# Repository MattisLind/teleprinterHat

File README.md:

# teleprinterHat
A RaspberryPi HAT that interfaces a old school teleprinter

## History
Some time ago I started planning to get an old Lorenz Lo15 teleprinter working. Then arose the question about how to interface those old machines to the real world. While investigating this I gained quite some knowledge of teleprinter interfacing and Telex networks. For example the normal line voltage of a US teleprinter line is 120VDC and the current is 60 mA.

Preferbly the interfacing should be as simple and small as possible. Using some big expensive 50 Hz 120 VAC transformer, rectifier and 2kOhm 6W resistor was not on the table.

Preferbly the circuit should be able to run off a standard USB charger. I.e. 5V 500mA. Experimenting a bit with a stepup circuit gave that is perfectly possibly to step up 5V to 120V. SO one could ask how could a 5V 500 mA supply be able to supply the power for a 120V 60mA load. Of course it cannot, but the problem lies in the fact tat most of the power is absorbed in the current limiting 2kOhm resistor of the old school circuit. The actual teleprinter has an internal resistance of approximately 100 Ohm. So why 120V? The reason for 120V is to achieve a fast pull of the magnet inside the teleprinter. After the initial pull the steady state voltage drop is between 5 to 10 V at 60mA. 

When I started to work with this project I also made an announcment in the i-Telex forum and got a reply from Jochen that had done something similar and the same point in time. What a coincidence! [piTelex project](https://github.com/fablab-wue/piTelex)

Jochen have compiled a lot of interesting and useful information there but the project is based on a Raspberry Pi and cannt be used stand alone. One of my requirements are that it should be able to run completely stand alone. I don't want the bloat of a Linux kernel just to push a few bytes back and forth!

## Requirments

So I put together a list of requirments

1. Shall only need 5V supply. The generation of up 120V DC is built into the device. Using a step-up converter.
2. Low power consumption. No 6W 2kOhm resistor. Use PWM to control the current through the solenoid. 
3. Configurable for 60mA, 40mA and 20mA current loop.
4. ~~Automatically detect the line voltage to use based on line current and required rise time of current through coil. Measure what kinde of loop inductance there is and adapt to a possibly resistive remote.~~ Deemed not possible with current design.
5. Interface directly to RS-232-E levels on board. (option) using a MAX232 or equivalent and a couple of capacitors
6. Interface directly to USB using FTDI chip on board (option)
7. Do baudot to ASCII conversion locally.
8. Do baudrate adaption locally. Configurable teleprinter baudrate to support at least 45,5, 50, 56, 75, 100 and 110 bps.
9. Configurable uplink RS-232 interface 50, 75, 110, 150, 300 bps to adapt to all sorts of hosts.
10. Dimensions that fits the Rpi Zero preferbly but if it is getting to crammed a standar Rpi HAT is the choice.
11. The RPI should be able to control all settings of the device from GPIO ports. Possibly use SPI to make more advanced configuration possible.
13. LEDs connected to RPi GPIOs to indicate mode or state in RPi Software.
14. Jumpers connected to the RPI GPIOs to control the RPI software and selection om mode of operation.
15. The RPi shall automatically boot up and select operating mode depending on jumpers. For example i-Telex or news RSS, RasPi serial console. No interaction using screen or keyboard connected to the RPi shall be necessary.
16. Relay to support reversal of polarity of the line current (optional)
17. Be able to drive a SSR that can be used to enable power to the teleprinter
18. Diagnostic LED to indicate line malfunction. I.e. to detect an open loop 
19. Current loop interface to support old PDP-11 current loops using opto couplers.
20. Use two 2.5 mm mono plugs for interfacing the teleprinter.
21. Diagnostic LED to indicate what line voltage is selected. Maybe multicolor RGB LED?
22. RX and TX LEDs
23. Support for FSG device (optional)
24. A few test sequences are built in. Continous RY and "The quick brown fox jumps over the lazy dog"
25. Flow control using XON/XOFF, RTS/CTS or DSR/DTR. Selcteable using jumpers. Both via USB/FTDI or RS-232

## Stepup converter

The first thing to verify is that the idea of the step up converter was ok. I did a small circuit board to check the circuit and during this I found that the parameters of the coil si very importantant. It has to have a high enough Isat. Then the choice of MOSFET is important. The MOSFET has to full turn on at only 5V gate voltage which is what is available in this circuit. Thus Vgs(ON) is of high interest. Then to deliver as much of the 5V into the coil means that as little loss of energy in the MOSFET is important. The rDS(ON) is the parameter to look for. 

It turned out that this circuit worked well and could easily deliver 120VDC.

## Using PWM to control the selector magnet.

The main idea with this circuit is to generate the required 60mA with as litle loss as possible. By measuring the current in the loop using a small resistance and then hysteresis regulate the current using a PNP transistor as switch. The current is feed through a small inductor which will not saturate. 

As the switch transistor is swithced on the current in the inductor will increase with time. When it reach the upper hysteresis limit the transistor will switch off. The current in the inductance will continue to flow through the diode and the resistor. As the current reaches the lower limit the transistor will switch on again. 

The receiver magnet inductance will only come into play when going from sending a space bit to a mark bit. Then the large total inductance will keep the regulator switched on for several milliseconds depending on the inductance in the magenet. As soon as the line current level is reached the magnetcoil is fully saturated and will act as a pure resistance. The implementation is based on a op-amp for measuring the differential volatage of the current measuring resistor. Then a fast comparator with a 5% hysterisis band generates a square wave from the incoming sawtooth signal. This squarewave then drives the switch transistors. 

The transistor switch is composed of a PNP transistor as the main switch transistor and a NPN level cvonversion transistor driving the PNP transistor through a resistance.

The reference voltage to the hysteresis comparator is supplied from a PWM signal output of the mikroprocessor. Thereby making it possible to control the current level through software. The PWM signal is low pass filtered in a simple RC network and then buffered through a buffering op-amp.

I did a quick mockup with components at hand but it turned out that the comparator needed to be pretty fast and the transistor switch as well. It simply didn't work very well. I decided to try to do simulations in LTspice before doing further breadboarding. 

Searches on internet gave a decent circuit for a P-MOS FET based switch. Simulations in LTspice gave proper values for resistors and capacitors and it was time to make a peroper board.

Schematic.

The design also included an PNP and NPN transistor to handle keying of the sening signal.

A simple NPN transistor is used to key the current in the loop ON/OFF. This has to be done without any free-wheeling diode since otherwise the release of the magnet when swithcing of the current will be very much delayed and might not even happen at all. 

Initial tests showed good performance. It could regulate the desired current at varying line voltages without any problem.

This picture show the voltage over the measurement resistor. The scale is 100mV per division and the resistor is 51 ohm so the interval it is regulating over is +/- 2mA as designed.

Running the circuit with the actual Lorenz Lo15 teleprinter also yielded good results.

Keying the signal, 90V line voltage, 40 mA line current. The large spikes are created by the selector magnet as the switch cuts off. Had initial problems that the choosen PNP transistor was unable to cope with these. Intalled a 300 V PNP transistor and a MOV to handle the spikes. Worked well. But I am considering using a TVS instead.

This picture shows when regulating the 40mA output to the selector magnet when the line is in marking state.

## Prototyping the Step up converter and current source 

I already did a prototype of the step-up converter. But the MOSFET used was quite big and overdimensioned. I also wanted to use a proper gate driver as well as off load the micro controller doing the chore of keeping the PWM rate continuosly measuring the output voltage. A separate, very small, switch control IC, cheap as well, was a better choice. So I designed another prototype board to test out these concept as well as testing the current loop circuit.

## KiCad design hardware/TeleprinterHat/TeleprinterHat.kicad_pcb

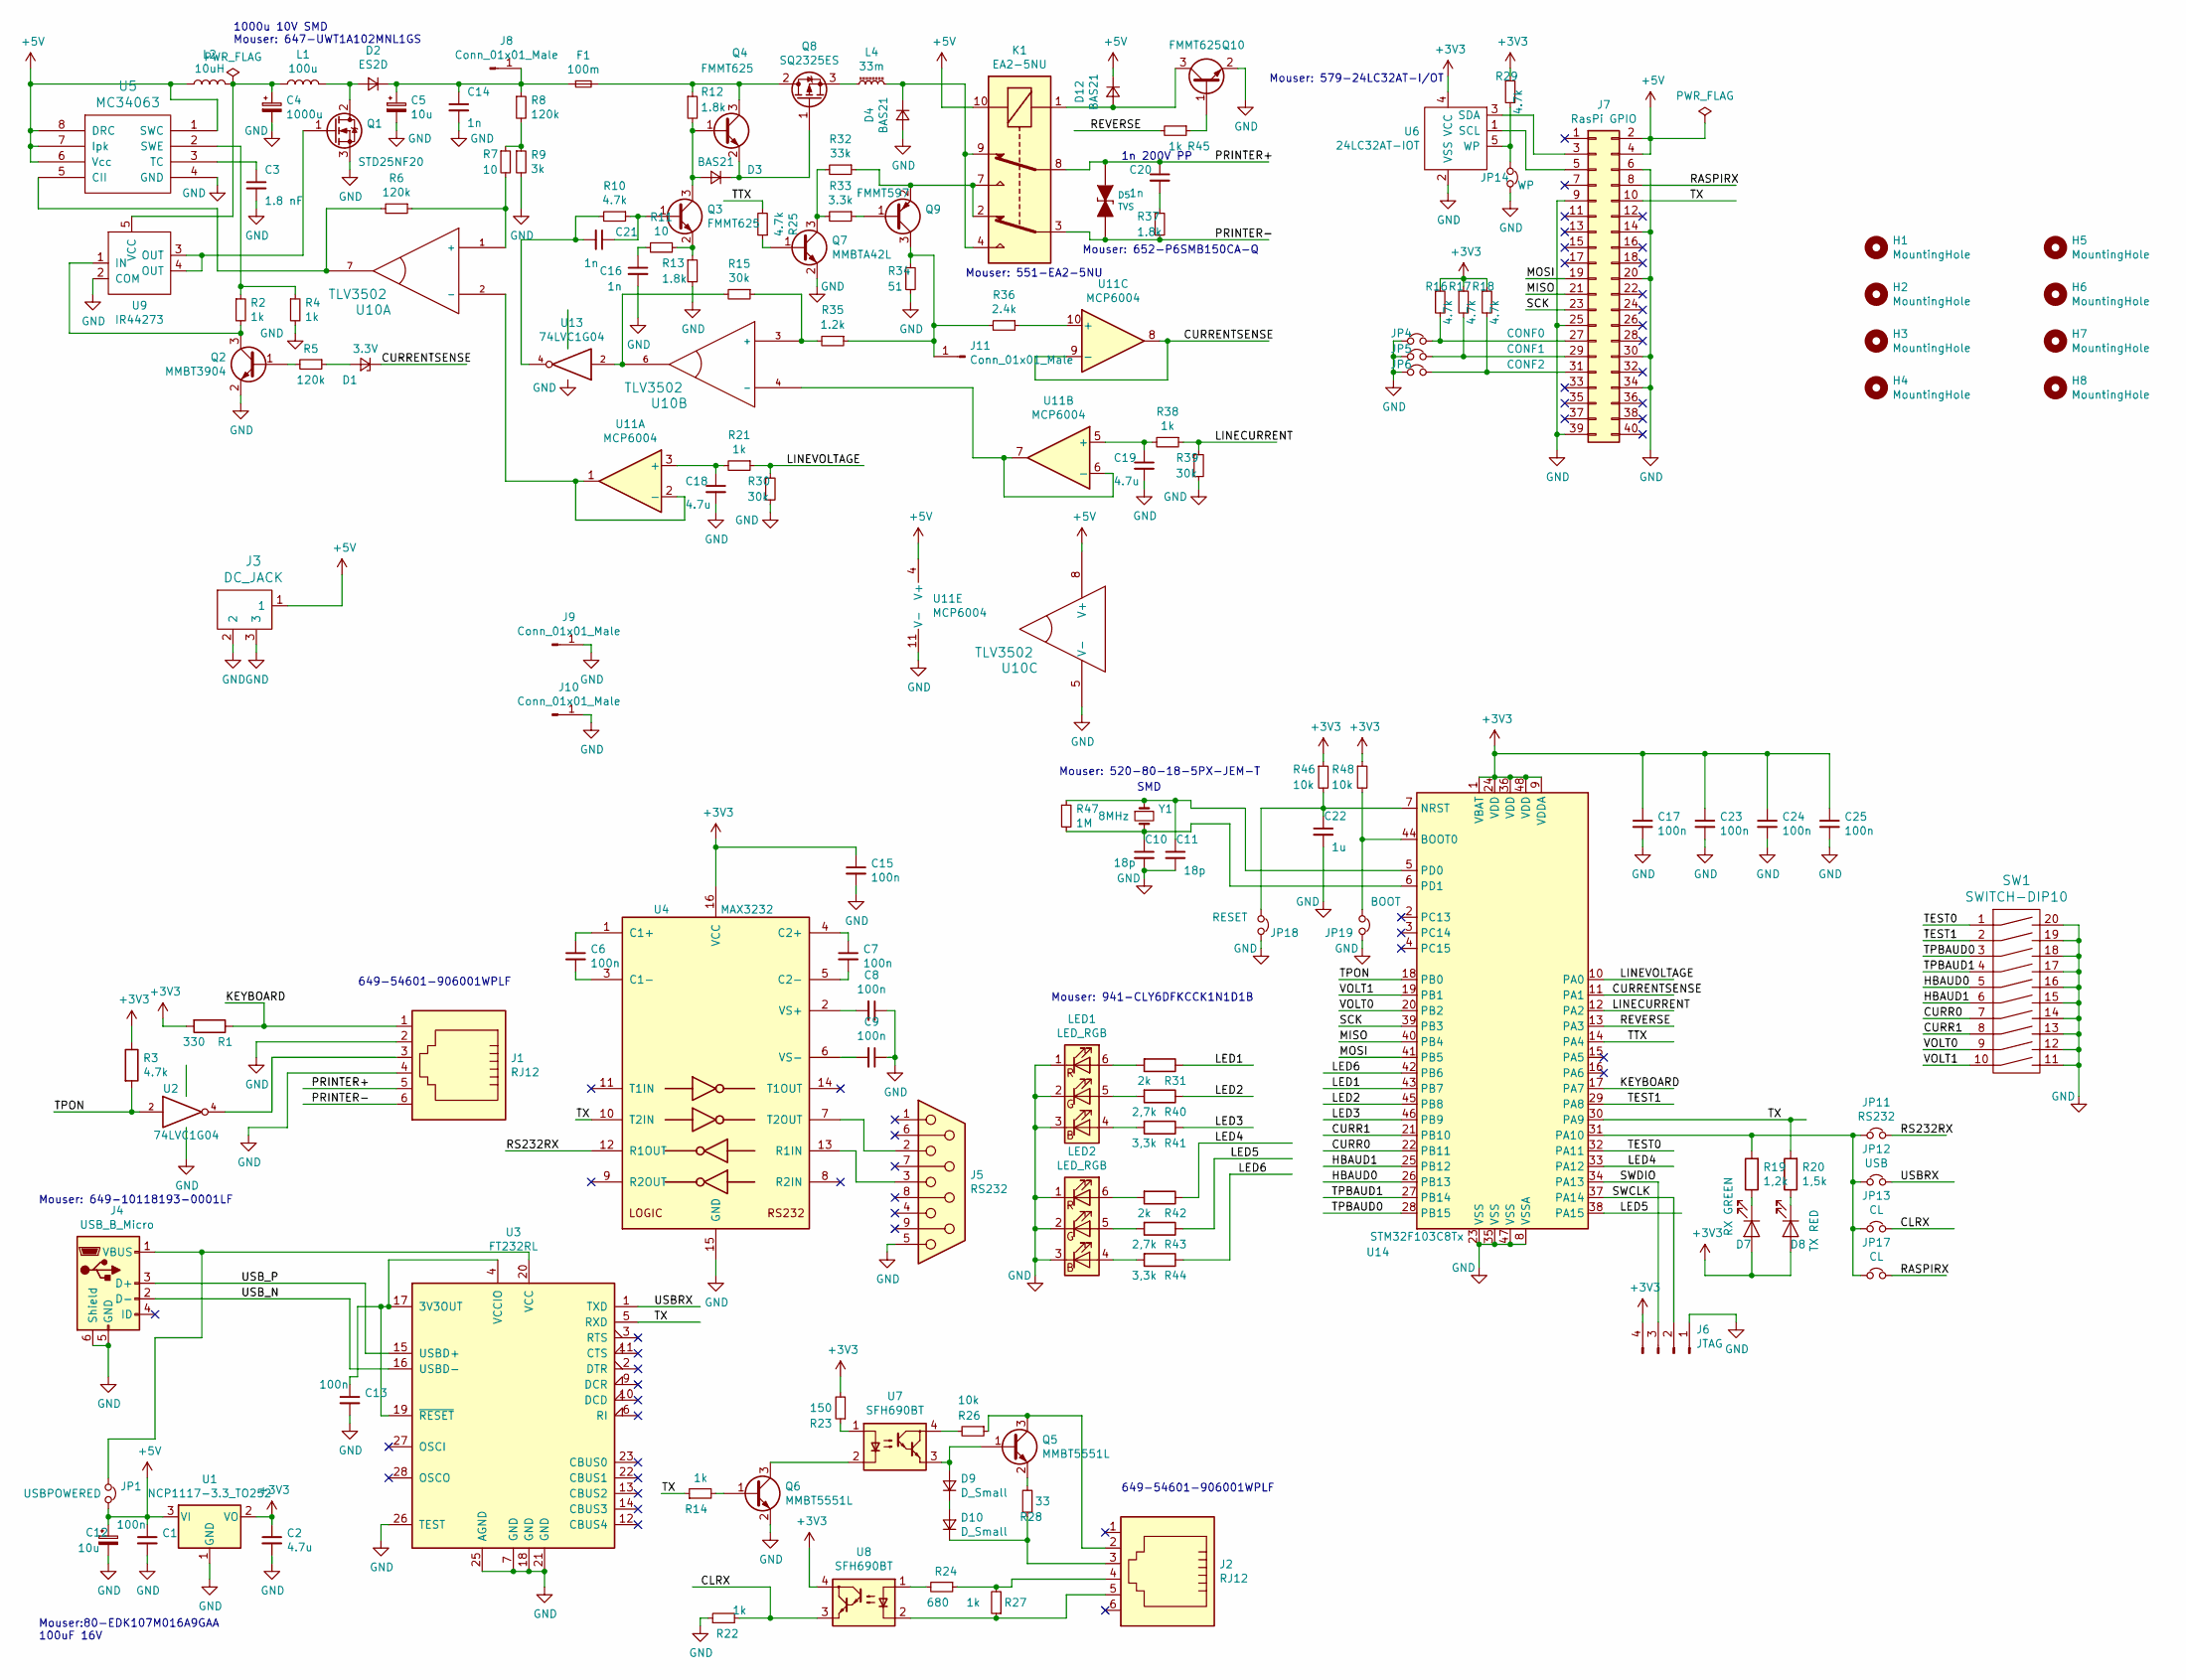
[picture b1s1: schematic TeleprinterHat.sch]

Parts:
C1, C6, C7, C8, C9, C13, C15, C17, C23, C24, C25: 100n; C_0805_2012Metric
C2, C18, C19: 4.7u; C_0805_2012Metric
C3: 1.8 nF; C_0805_2012Metric
C4: 1000u; CP_Elec_10x7.7
C5: 10u; CP_Radial_D8.0mm_P3.50mm
C10, C11: 18p; C_0805_2012Metric
C12: 10u; C_0805_2012Metric
C14, C16, C21: 1n; C_0805_2012Metric
C20: 1n; C_Rect_L7.0mm_W2.0mm_P5.00mm
C22: 1u; C_0805_2012Metric
D1: 3.3V; D_SOD-123
D2: ES2D; D_SMB_Handsoldering
D3, D4, D12: BAS21; SOT-23
D5: TVS; D_SMB_Handsoldering
D7: RX GREEN; LED_0805_2012Metric_Castellated
D8: TX RED; LED_0805_2012Metric_Castellated
D9, D10: D_Small; D_SOD-123
F1: 100m; Fuse_0603_1608Metric_Pad1.05x0.95mm_HandSolder
H1, H2, H3, H4, H5, H6, H7, H8: MountingHole; MountingHole_2.7mm_M2.5
J1, J2: RJ12; RJ12_Amphenol_54601
J3: DC_JACK; BarrelJack_Wuerth_6941xx301002
J4: USB_B_Micro; USB_Micro-B_Amphenol_10103594-0001LF_Horizontal
J5: RS232; DSUB-9_Female_Horizontal_P2.77x2.84mm_EdgePinOffset9.90mm_H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
J6: JTAG; PinHeader_1x04_P2.54mm_Vertical
J7: RasPi GPIO; PinSocket_2x20_P2.54mm_Vertical
J8, J9, J10, J11: Conn_01x01_Male; PinHeader_1x01_P2.54mm_Vertical
JP1: USBPOWERED; PinHeader_1x02_P2.54mm_Vertical
JP4: CONF0; PinHeader_1x02_P2.54mm_Vertical
JP5: CONF1; PinHeader_1x02_P2.54mm_Vertical
JP6: CONF2; PinHeader_1x02_P2.54mm_Vertical
JP11: RS232; PinHeader_1x02_P2.54mm_Vertical
JP12: USB; PinHeader_1x02_P2.54mm_Vertical
JP13, JP17: CL; PinHeader_1x02_P2.54mm_Vertical
JP14: WP; PinHeader_1x02_P2.54mm_Vertical
JP18: RESET; PinHeader_1x02_P2.54mm_Vertical
JP19: BOOT; PinHeader_1x02_P2.54mm_Vertical
K1: EA2-5NU; DIP-10_W7.62mm
L1: 100u; Wurth TIF Radial 1018
L2: 10uH; L_Radial_D7.0mm_P3.00mm
L4: 33m; L_Radial_D12.0mm_P6.00mm_MuRATA_1900R
LED1, LED2: LED_RGB; LED_Avago_PLCC6_3x2.8mm
Q1: STD25NF20; TO-252-3_TabPin2
Q2: MMBT3904; SOT-23
Q3, Q4, Q10: FMMT625; SOT-23
Q5, Q6: MMBT5551L; SOT-23
Q7: MMBTA42L; SOT-23
Q8: SQ2325ES; SOT-23
Q9: FMMT597; SOT-23
R1: 330; R_0805_2012Metric
R2, R4, R14, R21, R22, R27, R38, R45: 1k; R_0805_2012Metric
R3, R10, R16, R17, R18, R25, R29: 4.7k; R_0805_2012Metric
R5, R6, R8: 120k; R_0805_2012Metric
R7, R11: 10; R_0805_2012Metric
R9: 3k; R_0805_2012Metric
R12, R13, R37: 1.8k; R_0805_2012Metric
R15, R30, R39: 30k; R_0805_2012Metric
R19: 1,2k; R_0805_2012Metric
R20: 1,5k; R_0805_2012Metric
R23: 150; R_0805_2012Metric
R24: 680; R_0805_2012Metric
R26, R46, R48: 10k; R_0805_2012Metric
R28: 33; R_0805_2012Metric
R31, R42: 2k; R_0805_2012Metric
R32: 33k; R_0805_2012Metric
R33: 3.3k; R_0805_2012Metric
R34: 51; R_0805_2012Metric
R35: 1.2k; R_0805_2012Metric
R36: 2.4k; R_0805_2012Metric
R40, R43: 2,7k; R_0805_2012Metric
R41, R44: 3,3k; R_0805_2012Metric
R47: 1M; R_0805_2012Metric
SW1: SWITCH-DIP10; DIP-20_W7.62mm
U1: NCP1117-3.3_TO252; TO-252-2
U2, U13: 74LVC1G04; SOT-23-5_HandSoldering
U3: FT232RL; SSOP-28_5.3x10.2mm_P0.65mm
U4: MAX3232; SOIC-16_3.9x9.9mm_P1.27mm
U5: MC34063; SOIC-8_3.9x4.9mm_P1.27mm
U6: 24LC32AT-IOT; SOT-23-5_HandSoldering
U7, U8: SFH690BT; SO-4_4.4x3.6mm_P2.54mm
U9: IR44273; SOT-23-5_HandSoldering
U10: TLV3502; SOT-23-8_Handsoldering
U11: MCP6004; SOIC-14_3.9x8.7mm_P1.27mm
U14: STM32F103C8Tx; LQFP-48_7x7mm_P0.5mm
Y1: 8MHz; Crystal_SMD_HC49-SD

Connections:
+5V: C1.1, C12.1, D12.1 (K), J3.1, J7.2, J7.4, JP1.2, K1.10, L2.1, U1.3 (VI), U5.1 (SWC), U5.6 (Vcc), U5.7 (Ipk), U5.8 (DRC), U10.8 (V+), U11.4 (V+)
/CLRX: JP13.2, R22.2, U8.3
/CURR0: SW1.7, U14.22 (PB11)
/CURR1: SW1.8, U14.21 (PB10)
/CURRENTSENSE: D1.1 (K), U11.8, U11.9 (-), U14.11 (PA1)
/HBAUD0: SW1.5, U14.26 (PB13)
/HBAUD1: SW1.6, U14.25 (PB12)
/KEYBOARD: J1.1, R1.1, U14.17 (PA7)
/LED1: R31.1, U14.43 (PB7)
/LED2: R40.1, U14.45 (PB8)
/LED3: R41.1, U14.46 (PB9)
/LED4: R42.1, U14.33 (PA12)
/LED5: R43.1, U14.38 (PA15)
/LED6: R44.1, U14.42 (PB6)
/LINECURRENT: R38.1, R39.1, U14.12 (PA2)
/LINEVOLTAGE: R21.1, R30.1, U14.10 (PA0)
/MISO: J7.21, U14.40 (PB4)
/MOSI: J7.19, U14.41 (PB5)
/PRINTER+: C20.1, D5.1 (A), J1.5, K1.8
/PRINTER-: D5.2 (K), J1.6, K1.3, R37.2
/RASPIRX: J7.8, JP17.2
/REVERSE: R45.2, U14.13 (PA3)
/RS232RX: JP11.2, U4.12 (R1OUT)
/SCK: J7.23, U14.39 (PB3)
/TEST0: SW1.1, U14.32 (PA11)
/TEST1: SW1.2, U14.29 (PA8)
/TPBAUD0: SW1.3, U14.28 (PB15)
/TPBAUD1: SW1.4, U14.27 (PB14)
/TPON: R3.2, U2.2, U14.18 (PB0)
/TTX: R25.2, U14.14 (PA4)
/TX: J7.10, R14.1, R20.2, U3.5 (RXD), U4.10 (T2IN), U14.30 (PA9)
/USBRX: JP12.2, U3.1 (TXD)
/USB_N: J4.2 (D-), U3.16 (USBD-)
/USB_P: J4.3 (D+), U3.15 (USBD+)
/VOLT0: SW1.9, U14.20 (PB2)
/VOLT1: SW1.10, U14.19 (PB1)
unnamed: C3.1, U5.3 (TC)
unnamed: C4.1, L1.1, L2.2, U9.5 (VCC)
unnamed: C6.1, U4.1 (C1+)
unnamed: C6.2, U4.3 (C1-)
unnamed: C7.1, U4.4 (C2+)
unnamed: C7.2, U4.5 (C2-)
unnamed: C8.2, U4.2 (VS+)
unnamed: C9.2, U4.6 (VS-)
unnamed: C10.1, R47.2, U14.6 (PD1), Y1.2
unnamed: C11.1, R47.1, U14.5 (PD0), Y1.1
unnamed: C13.1, U3.4 (VCCIO), U3.17 (3V3OUT), U3.19 (~RESET~)
unnamed: C5.1, C14.1, D2.1 (K), F1.1, J8.1, R8.1
unnamed: C16.1, R11.2
unnamed: C18.1, R21.2, U11.3 (+)
unnamed: C19.1, R38.2, U11.5 (+)
unnamed: C20.2, R37.1
unnamed: C21.1, Q3.1 (B), R10.1
unnamed: C21.2, R10.2, U13.4
unnamed: C22.1, JP18.1, R46.2, U14.7 (NRST)
unnamed: D1.2 (A), R5.1
unnamed: D2.2 (A), L1.2, Q1.2 (D)
unnamed: D3.1 (K), Q4.2 (E), Q8.1 (G)
unnamed: D3.2 (A), Q3.3 (C), Q4.1 (B), R12.2
unnamed: D4.1 (K), K1.4, K1.9, L4.2
unnamed: D9.2 (A), Q5.1 (B), U7.3
unnamed: D10.1 (K), J2.3, R28.1
unnamed: D9.1 (K), D10.2 (A)
unnamed: D12.2 (A), K1.1, Q10.3 (C)
unnamed: F1.2, Q4.3 (C), Q8.2 (D), R12.1
unnamed: J1.3, U2.4
unnamed: J2.2, Q5.3 (C), R26.1
unnamed: J2.4, R24.1, R27.2
unnamed: J2.5, R27.1, U8.2
unnamed: J4.1 (VBUS), JP1.1, U3.20 (VCC)
unnamed: J5.2, U4.7 (T2OUT)
unnamed: J5.3, U4.13 (R1IN)
unnamed: J7.3, U6.3 (SDA)
unnamed: J7.5, U6.1 (SCL)
unnamed: J7.27, JP4.2, R16.2
unnamed: J7.29, JP5.2, R17.2
unnamed: J7.31, JP6.2, R18.2
unnamed: J11.1, Q9.3 (C), R34.1, R35.1, R36.2
unnamed: JP11.1, JP12.1, JP13.1, JP17.1, R19.2, U14.31 (PA10)
unnamed: JP14.1, R29.2, U6.5 (WP)
unnamed: JP19.1, R48.2, U14.44 (BOOT0)
unnamed: K1.2, K1.7, Q9.2 (E), R32.1
unnamed: L4.1, Q8.3 (S)
unnamed: LED1.4 (BA), R41.2
unnamed: LED1.5 (GA), R40.2
unnamed: LED1.6 (RA), R31.2
unnamed: LED2.4 (BA), R44.2
unnamed: LED2.5 (GA), R43.2
unnamed: LED2.6 (RA), R42.2
unnamed: Q1.1 (G), U9.3 (OUT), U9.4 (OUT)
unnamed: Q2.1 (B), R5.2
unnamed: Q2.3 (C), R2.2, U9.1 (IN)
unnamed: Q3.2 (E), R11.1, R13.1
unnamed: Q5.2 (E), R28.2
unnamed: Q6.1 (B), R14.2
unnamed: Q6.3 (C), U7.2
unnamed: Q7.1 (B), R25.1
unnamed: Q7.3 (C), R32.2, R33.2
unnamed: Q9.1 (B), R33.1
unnamed: Q10.1 (B), R45.1
unnamed: R2.1, R4.1, U5.2 (SWE)
unnamed: R6.1, R7.2, U10.1 (+)
unnamed: R6.2, U5.5 (CII), U10.7
unnamed: R7.1, R8.2, R9.1
unnamed: R15.1, R35.2, U10.3 (+)
unnamed: R15.2, U10.6, U13.2
unnamed: R23.1, U7.1
unnamed: R24.2, U8.1
unnamed: R26.2, U7.4
unnamed: R36.1, U11.10 (+)
unnamed: U10.2 (-), U11.1, U11.2 (-)
unnamed: U10.4 (-), U11.6 (-), U11.7

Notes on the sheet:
Mouser: 551-EA2-5NU
Mouser: 941-CLY6DFKCCK1N1D1B
SMD
1n 200V PP
Mouser: 649-10118193-0001LF
1000u 10V SMD Mouser: 647-UWT1A102MNL1GS
Mouser: 520-80-18-5PX-JEM-T
Mouser: 579-24LC32AT-I/OT
Mouser:80-EDK107M016A9GAA 100uF 16V
Mouser: 652-P6SMB150CA-Q
649-54601-906001WPLF

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
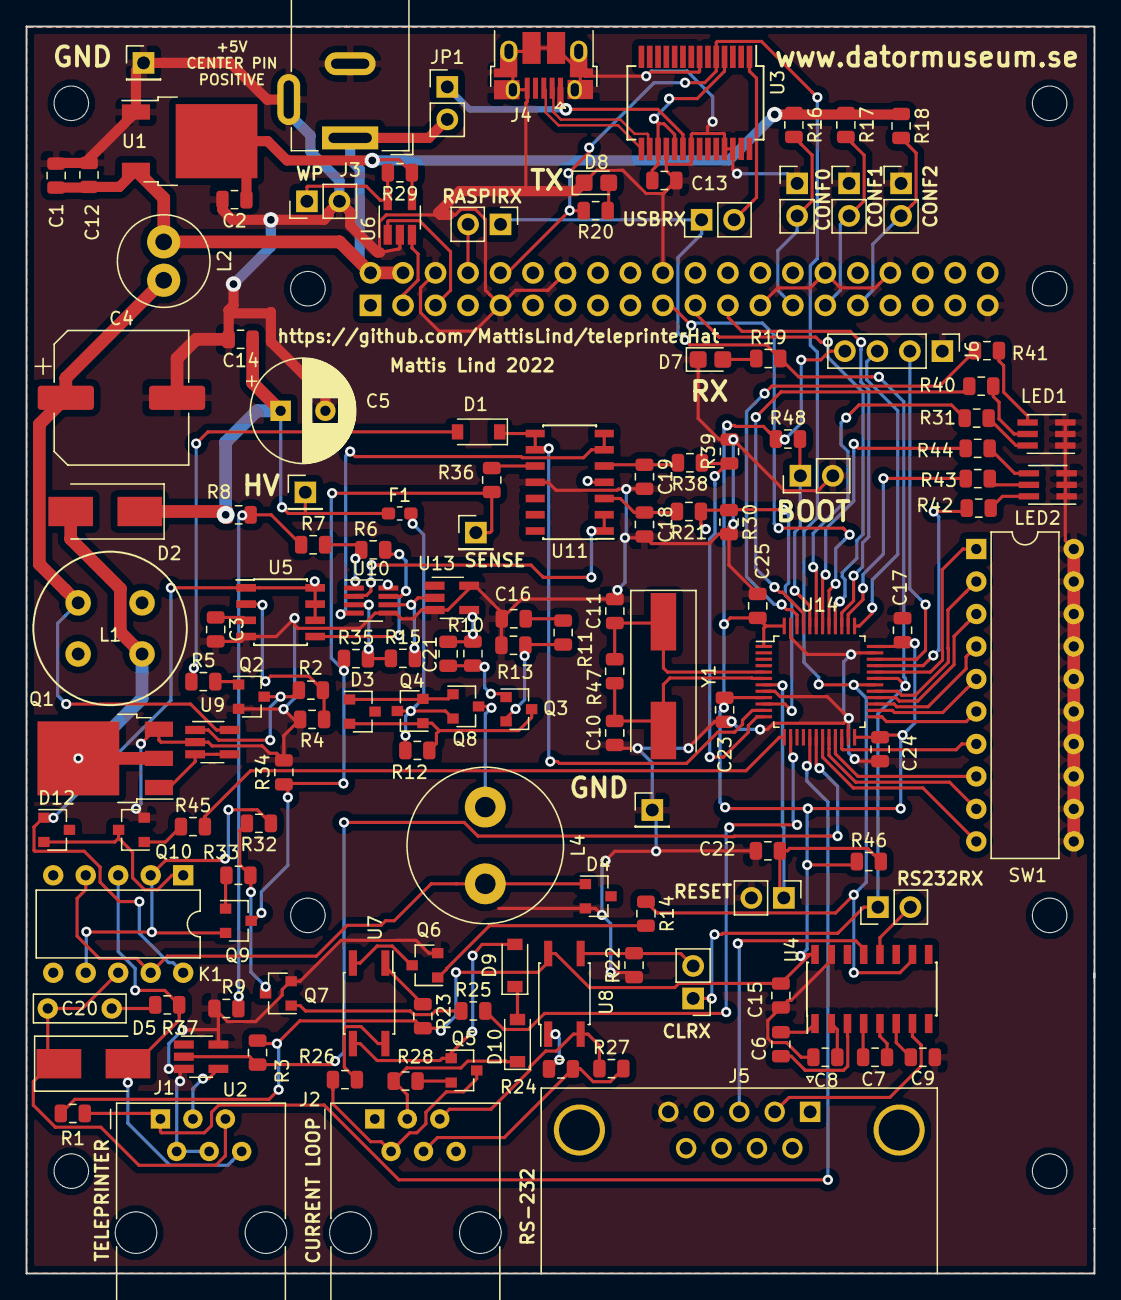
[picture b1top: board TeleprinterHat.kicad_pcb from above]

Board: 2 copper layers, 83.5 x 97.5 mm, 145 parts (1 on the bottom side), 118 nets.

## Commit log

2019-04-01 First commit of requiremnents.
2019-04-01 Adding info on the Step up converter and PVM idea.
2019-06-21 Just a quick hack for testing.
2019-06-21 Added more pictures on the prototypes
2019-06-21 Fixed the wrong picture.
2019-06-21 Added the prototype step up converter schematic
2019-06-21 LO15 not LO15b
2019-06-22 Added a small stupid unit test to see that the code for handling baudot conversionand buffering worked. Buffering did work but not the baudot conversion so some bugfixing was needed, which havt to go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
2019-06-22 Added code and test case for the tx state machine
2019-06-23 First try at a uart rx receiver.
2019-06-23 Moving files a bit.
2019-06-23 Major refactoring into several differnt modules.
2019-06-24 Changed name.
2019-06-24 Refactored out baudot encoding.
2019-06-24 Clean up
2019-06-24 Refactor array init.
2019-06-24 More refactor.
2019-06-28 Added test code for the receiver portion. The sent serial data is echoed back into the receiver
2019-06-28 Spelling fixes...
2019-06-30 Moving around files to make the Arduino environment happy.
2019-06-30 Added flow control requirement. Rm req for auto coil detection
2019-06-30 First try to get the STM32 code working.
2019-06-30 The bit order was reversed.
2019-06-30 Fixed to use another output. Fixed sample rate.
2019-07-01 CR and LF was shifted.
2019-07-01 Updated test case to reflect the changed directory setup
2019-07-01 Fixes
2019-07-03 Filtering of the input signal to avoid short glitches.
2019-07-06 Debuging. Got the figures table a bit wrong some how. The sampleCOunter was not cleared which made sampling happen to early
2019-07-06 Fixed more mapping errors.
2020-05-10 Added a note on what environment to use when compiling in Arduino - Hard to remember and is not stored in some project file unfortunately.
2021-01-21 Added schematic for the full solution.
2021-04-25 Ready for routing board.
2022-01-17 Almost ready!
2022-04-23 Added pdf and SVG
2022-04-24 Rotated the SVG.
2022-04-24 White background.
2022-04-24 Revert viewbox change.
2022-04-24 Change size.
2022-04-24 First spin of the board - has a few small issues.
